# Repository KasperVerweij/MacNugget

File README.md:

# BlueSCSI Mini PCB Clone

A compact STM32-based PCB clone of the BlueSCSI project - a personal hardware experiment.

## Overview

This is a smaller form-factor version of the BlueSCSI hardware design, created as a fun PCB project experiment. It implements the core BlueSCSI functionality in a more compact layout.

## Important Limitations

⚠️ **This board lacks SCSI termination circuitry** - As a result, it does not work reliably on all machines. 

### Compatibility

- ✅ **Confirmed Working:** PowerMac systems
- ❓ **Limited Testing:** Other SCSI devices may or may not work depending on their termination requirements

## Project Status

This is a personal experimental project created for learning and fun. It is **not a commercial product** and is not intended for sale.

## Credits

This project uses the excellent **[BlueSCSI](https://github.com/BlueSCSI/BlueSCSI-v2)** firmware.

**Full credit goes to the BlueSCSI team** for their amazing work on the firmware and original hardware design. This PCB is simply a hardware variant/experiment based on their groundwork.

## Disclaimer

This is an unofficial clone/modification. For a fully-featured, tested, and supported BlueSCSI solution, please visit the official BlueSCSI project.

## License

Hardware files follow their own licensing terms. The BlueSCSI firmware retains its original license from the BlueSCSI project.

---

*This is a hobbyist project - use at your own risk!*

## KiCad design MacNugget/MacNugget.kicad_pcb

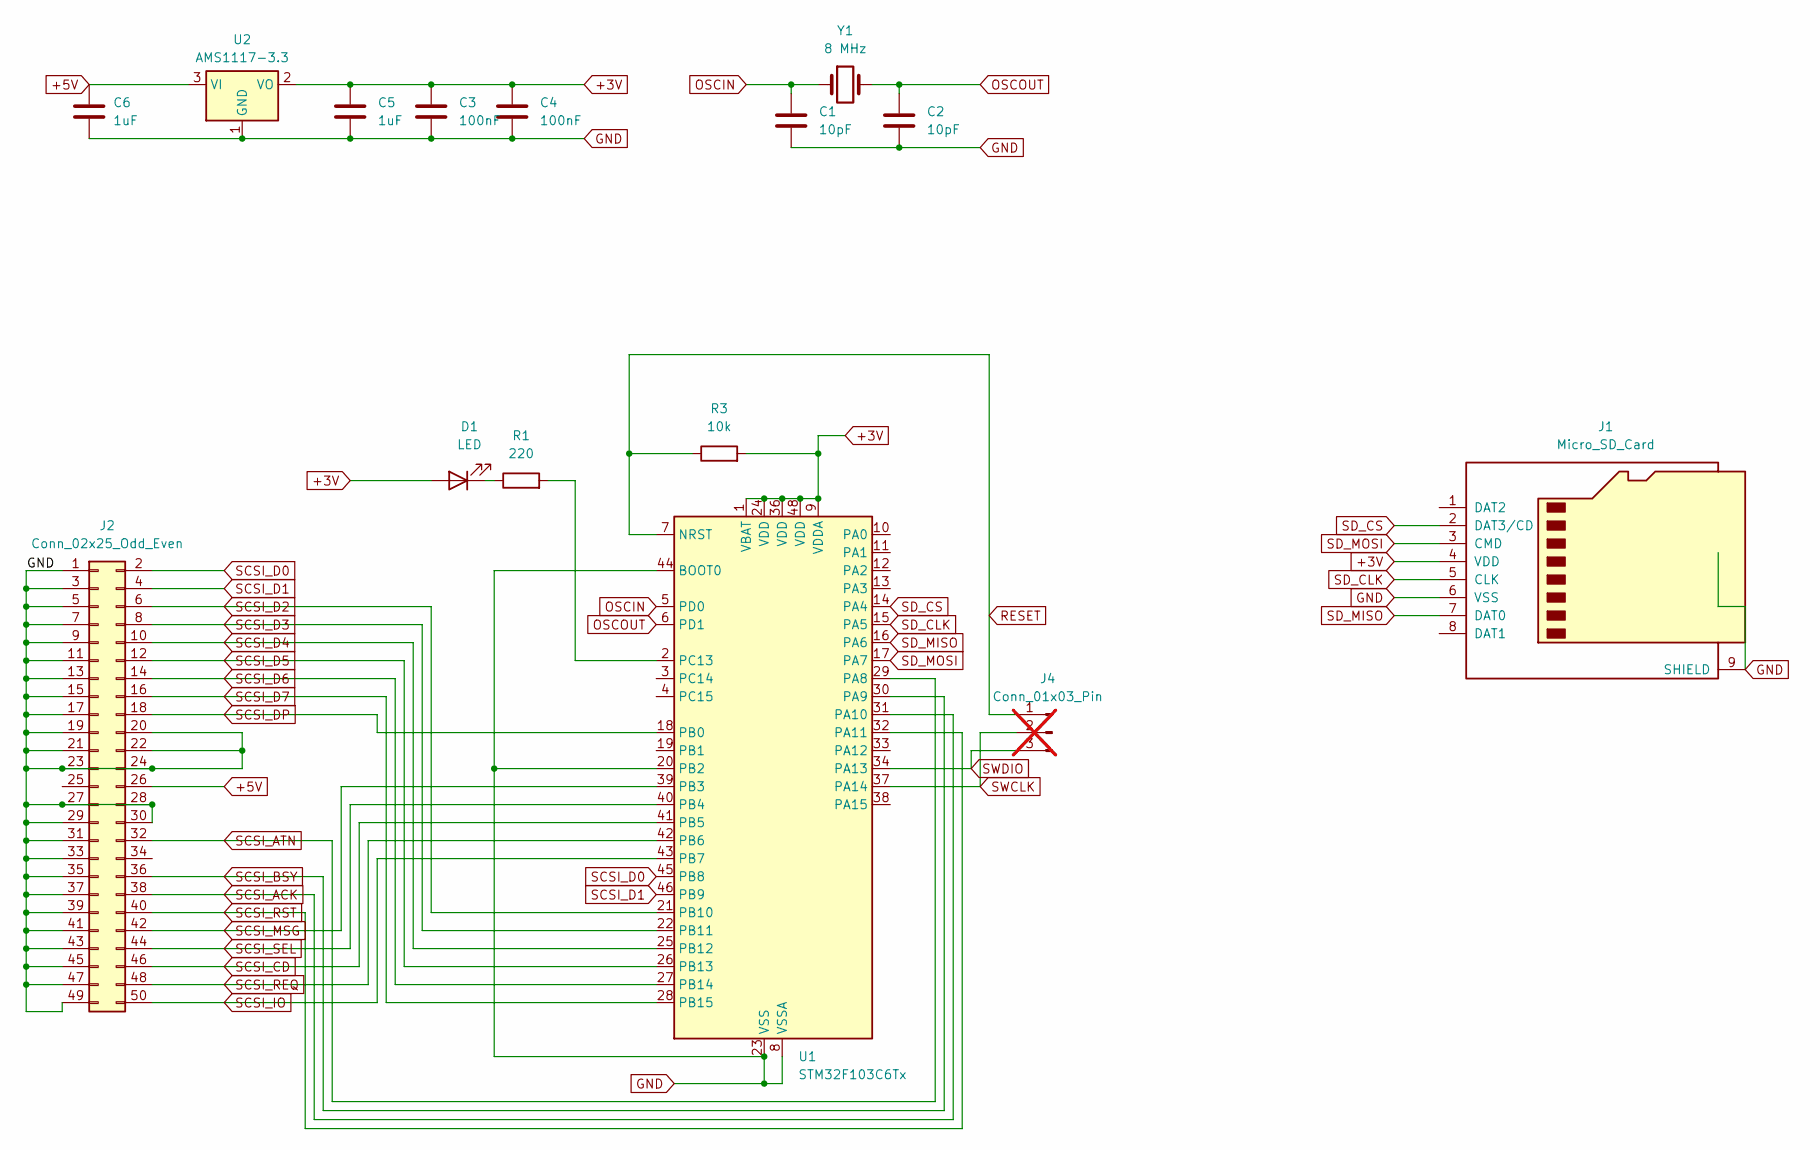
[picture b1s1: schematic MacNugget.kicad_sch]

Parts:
C1, C2: 10pF; C_0603_1608Metric
C3, C4: 100nF; C_0603_1608Metric
C5, C6: 1uF; C_0805_2012Metric
D1: LED; LED_0805_2012Metric
J1: Micro_SD_Card; microSD_HC_Molex_47219-2001
J2: Conn_02x25_Odd_Even; PinHeader_2x25_P2.54mm_Vertical
J4: Conn_01x03_Pin; PinSocket_1x03_P2.54mm_Vertical; not fitted
R1: 220; R_0603_1608Metric
R3: 10k; R_0603_1608Metric
U1: STM32F103C6Tx; LQFP-48_7x7mm_P0.5mm
U2: AMS1117-3.3; SOT-223-3_TabPin2
Y1: 8 MHz; Crystal_HC49-4H_Vertical

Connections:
+3V: C3.1, C4.1, C5.1, D1.2 (A), J1.4 (VDD), R3.2, U1.1 (VBAT), U1.9 (VDDA), U1.24 (VDD), U1.36 (VDD), U1.48 (VDD), U2.2 (VO)
+5V: C6.1, J2.26, U2.3 (VI)
GND: C1.2, C2.2, C3.2, C4.2, C5.2, C6.2, J1.6 (VSS), J1.9 (SHIELD), J2.1, J2.3, J2.5, J2.7, J2.9, J2.11, J2.13, J2.15, J2.17, J2.19, J2.20, J2.21, J2.22, J2.23, J2.24, J2.27, J2.28, J2.29, J2.30, J2.31, J2.33, J2.35, J2.37, J2.39, J2.41, J2.43, J2.45, J2.47, J2.49, U1.8 (VSSA), U1.20 (PB2), U1.23 (VSS), U1.35 (VSS), U1.44 (BOOT0), U1.47 (VSS), U2.1 (GND)
unnamed: D1.1 (K), R1.1
unnamed: R1.2, U1.2 (PC13)
OSCIN: C1.1, U1.5 (PD0), Y1.1
OSCOUT: C2.1, U1.6 (PD1), Y1.2
RESET: J4.1, R3.1, U1.7 (NRST)
SCSI_ACK: J2.38, U1.31 (PA10)
SCSI_ATN: J2.32, U1.29 (PA8)
SCSI_BSY: J2.36, U1.30 (PA9)
SCSI_CD: J2.46, U1.41 (PB5)
SCSI_D0: J2.2, U1.45 (PB8)
SCSI_D1: J2.4, U1.46 (PB9)
SCSI_D2: J2.6, U1.21 (PB10)
SCSI_D3: J2.8, U1.22 (PB11)
SCSI_D4: J2.10, U1.25 (PB12)
SCSI_D5: J2.12, U1.26 (PB13)
SCSI_D6: J2.14, U1.27 (PB14)
SCSI_D7: J2.16, U1.28 (PB15)
SCSI_DP: J2.18, U1.18 (PB0)
SCSI_IO: J2.50, U1.43 (PB7)
SCSI_MSG: J2.42, U1.39 (PB3)
SCSI_REQ: J2.48, U1.42 (PB6)
SCSI_RST: J2.40, U1.32 (PA11)
SCSI_SEL: J2.44, U1.40 (PB4)
SD_CLK: J1.5 (CLK), U1.15 (PA5)
SD_CS: J1.2 (DAT3/CD), U1.14 (PA4)
SD_MISO: J1.7 (DAT0), U1.16 (PA6)
SD_MOSI: J1.3 (CMD), U1.17 (PA7)
SWCLK: J4.2, U1.37 (PA14)
SWDIO: J4.3, U1.34 (PA13)

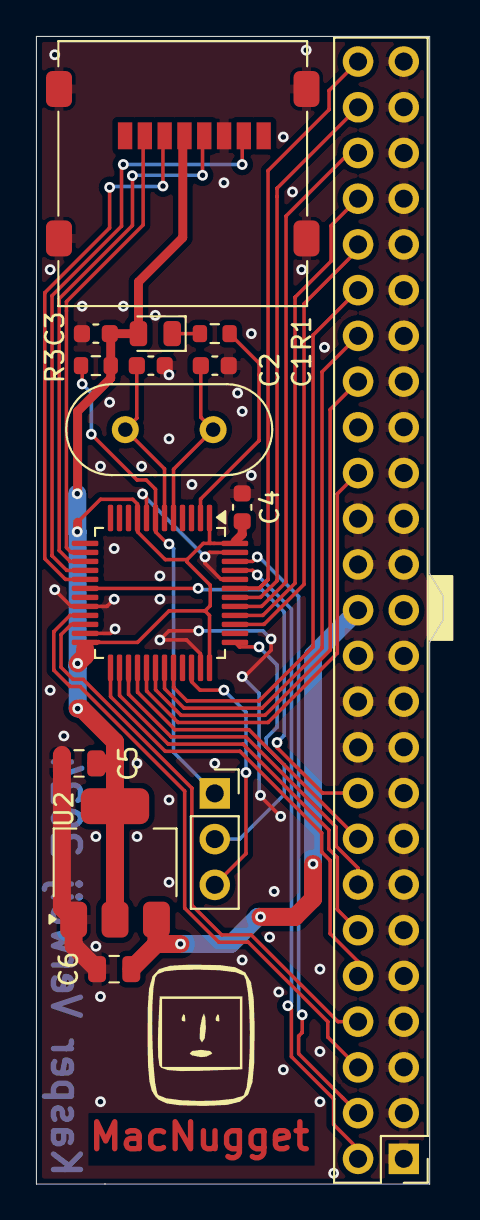
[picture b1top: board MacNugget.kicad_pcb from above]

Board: 2 copper layers, 22.6 x 63.8 mm, 15 parts (0 on the bottom side), 32 nets.

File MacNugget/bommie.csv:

"Reference";"Value";"Datasheet";"Footprint";"Qty";"DNP"
"C1,C2";"10pF";"~";"Capacitor_SMD:C_0603_1608Metric";"2";""
"C3,C4";"100nF";"~";"Capacitor_SMD:C_0603_1608Metric";"2";""
"C5,C6";"1uF";"~";"Capacitor_SMD:C_0805_2012Metric";"2";""
"D1";"LED";"~";"LED_SMD:LED_0805_2012Metric";"1";""
"J1";"Micro_SD_Card";"http://katalog.we-online.de/em/datasheet/693072010801.pdf";"Connector_Card:microSD_HC_Hirose_DM3D-SF";"1";""
"J2";"Conn_02x25_Odd_Even";"~";"Connector_PinHeader_2.54mm:PinHeader_2x25_P2.54mm_Vertical";"1";""
"J4";"Conn_01x03_Pin";"~";"Connector_PinSocket_2.54mm:PinSocket_1x03_P2.54mm_Vertical";"1";"DNP"
"R1";"220";"~";"Resistor_SMD:R_0603_1608Metric";"1";""
"R3";"10k";"~";"Resistor_SMD:R_0603_1608Metric";"1";""
"U1";"STM32F103C6Tx";"https://www.st.com/resource/en/datasheet/stm32f103c6.pdf";"Package_QFP:LQFP-48_7x7mm_P0.5mm";"1";""
"U2";"AMS1117-3.3";"http://www.advanced-monolithic.com/pdf/ds1117.pdf";"Package_TO_SOT_SMD:SOT-223-3_TabPin2";"1";""
"Y1";"8 MHz";"~";"Crystal:Crystal_HC49-4H_Vertical";"1";""

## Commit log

2026-02-04 Uploaded the project
    Haven't worked on this in ages, so this is more archive
2026-02-04 Initialize README with project information
    Added project details, limitations, compatibility, and credits.
2026-02-04 Add image to README for BlueSCSI Mini PCB Clone
    Added an image to the README for visual reference.
